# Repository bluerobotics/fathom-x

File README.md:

# Fathom-X and Fathom-E

The Fathom-X and -E Tether Boards are part of Blue Robotics' *Fathom Tether* system. These boards provide interfaces and functionality for the communication methods used with the tether. With the Fathom tether, it is quick and easy to get up and running and interface with your ROV or other application.

The schematic and board layout are designed in EagleCAD.

# Fathom-E (Simple Ethernet) Hardware

## Description

The Fathom-E board provides a simple and economical way to connect the Fathom Tether or a Cat5 cable to an Ethernet jack. It uses all four twisted pairs in the cable and works for tether lengths of up to 100m (per the Ethernet specification).

# Fathom-X Hardware

The Fathom-X board has a few advantages over the Fathom-E interface. It uses a HomePlugAV (IEEE1901) module to send 100 Mbps Ethernet with a single twisted pair. This robust connection works over at least 300m tether lengths. 

Please see the [official documentation](http://docs.bluerobotics.com/fathom-x/) for more information.

## License

The Fathom Ethernet Hardware Design is released under the MIT License.

## Revision History

### Fathom-E 

rev1 - Works but RJ45 misaligned

rev2 - Production version

### Fathom-X

rev1 - Works but poor tether connector used

rev2 - Production version with updated connector

RevB - In progress

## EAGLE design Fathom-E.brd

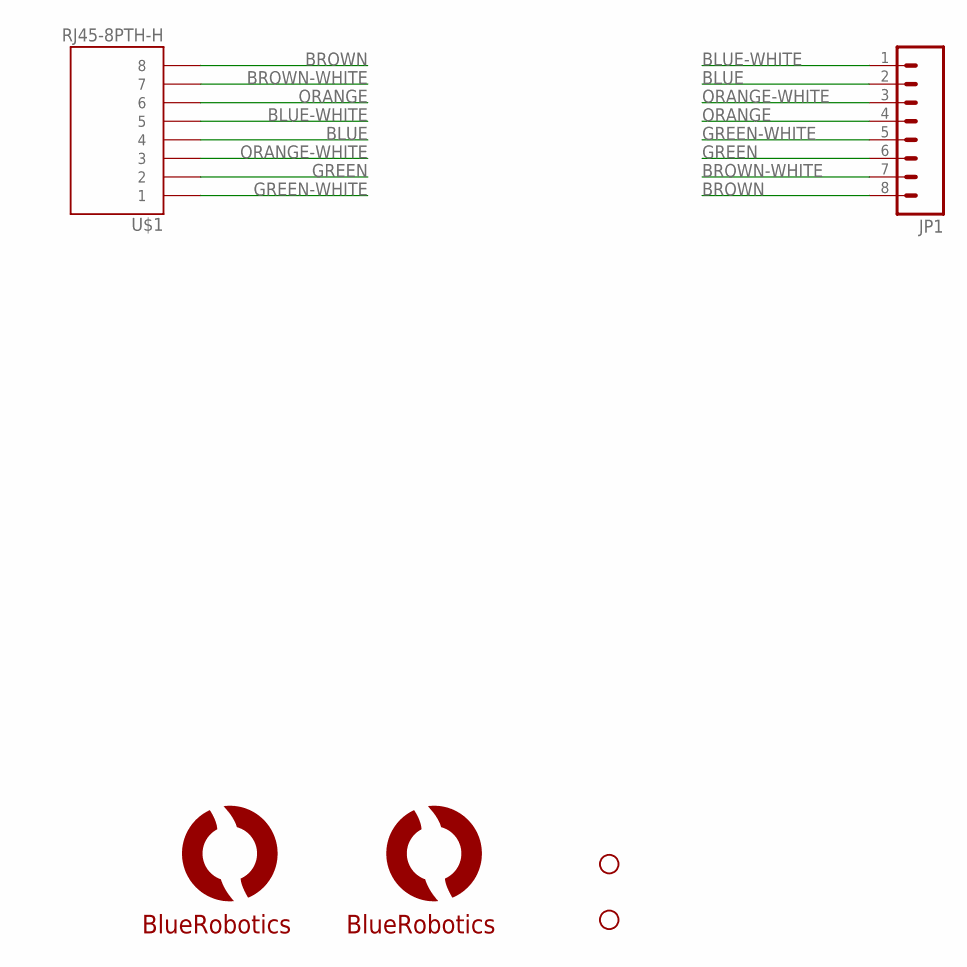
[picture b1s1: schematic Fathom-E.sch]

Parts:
JP1: M083.5MM-8; SCREWTERMINAL-3.5MM-8
STANDOFF2, STANDOFF3: STAND-OFF
U$1: RJ45-8PTH-H; RJ45-8
U$6: LOGOBR-LOGO-MS-COPPER; BR-LOGO-MEDIUM-SMALL-COPPER
U$7: LOGOFULL-M; BR-FULL-LOGO-MEDIUM

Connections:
BLUE: JP1.2, U$1.4
BLUE-WHITE: JP1.1, U$1.5
BROWN: JP1.8, U$1.8
BROWN-WHITE: JP1.7, U$1.7
GREEN: JP1.6, U$1.2
GREEN-WHITE: JP1.5, U$1.1
ORANGE: JP1.4, U$1.6
ORANGE-WHITE: JP1.3, U$1.3

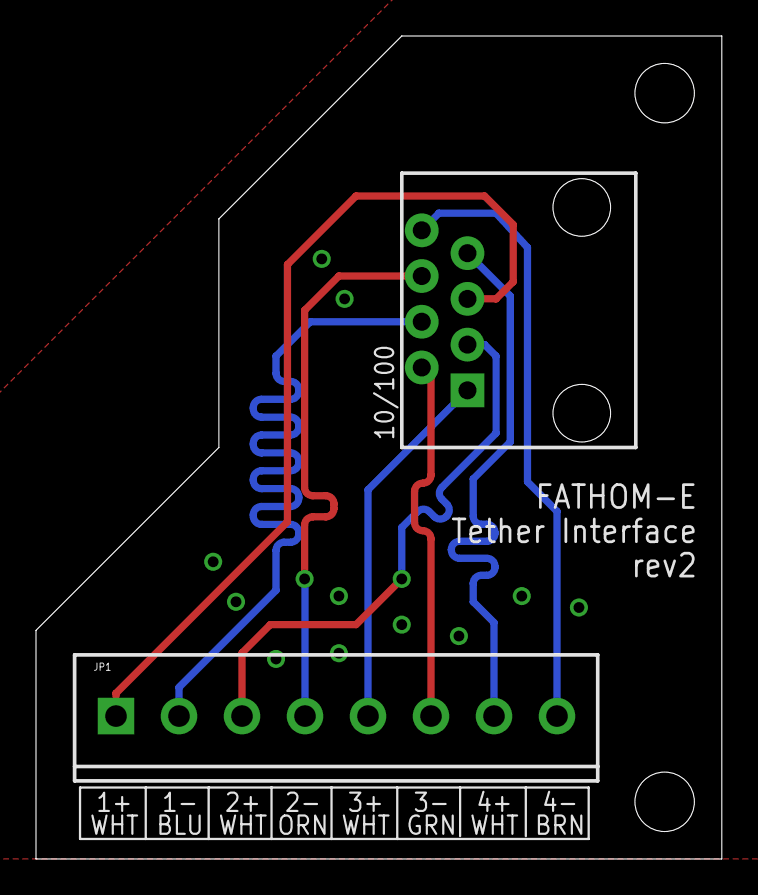
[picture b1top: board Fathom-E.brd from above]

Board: 2 copper layers, 38.1 x 45.7 mm, 6 parts (1 on the bottom side), 8 nets.

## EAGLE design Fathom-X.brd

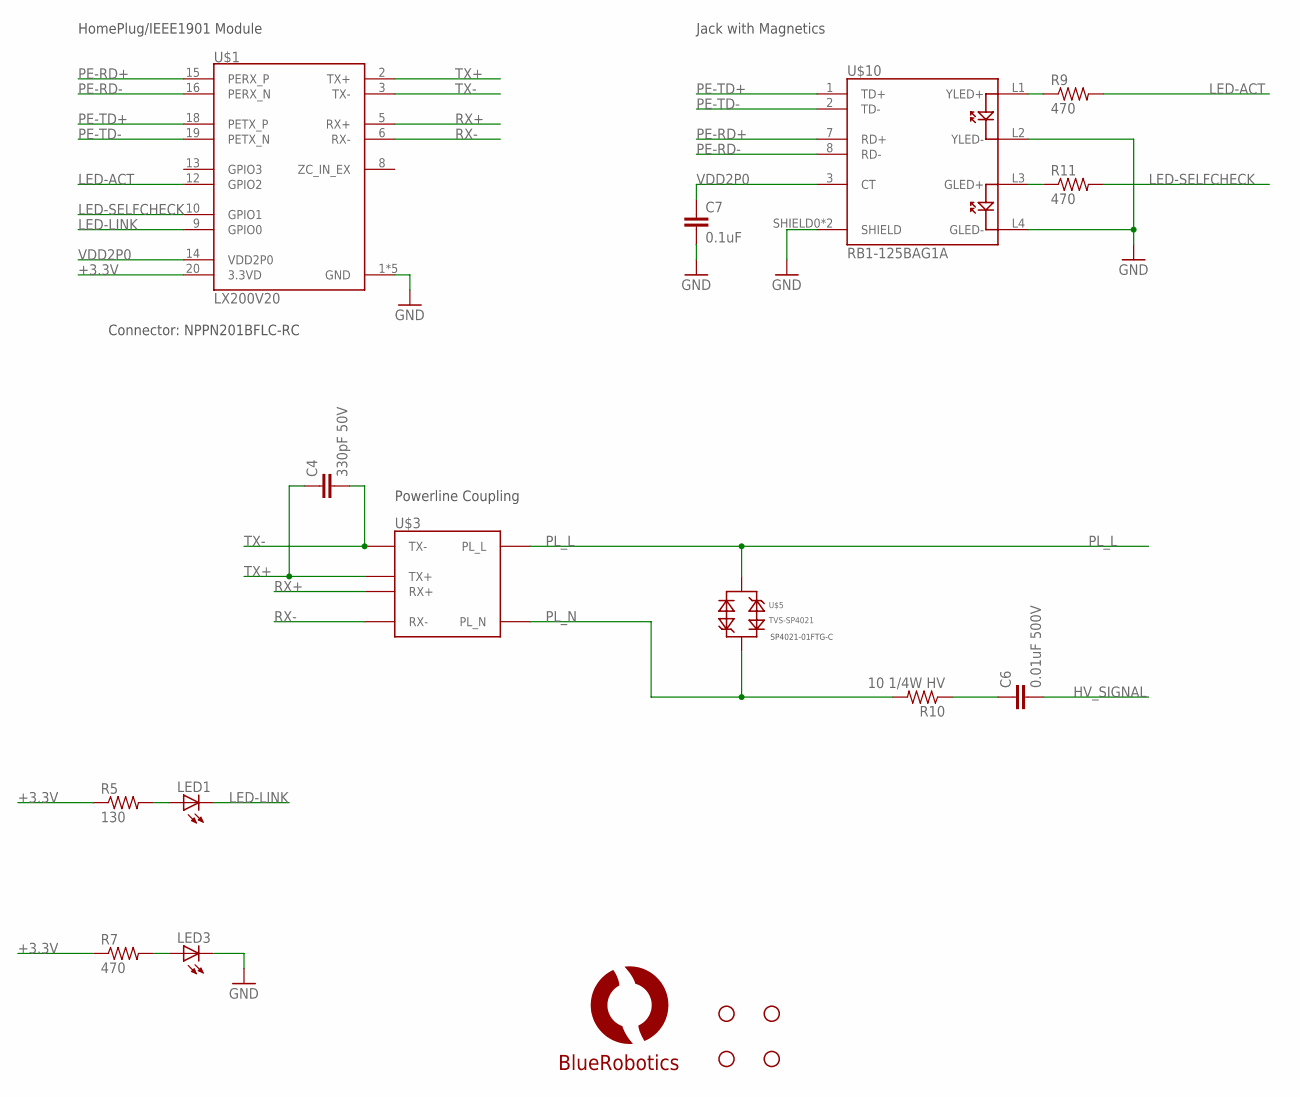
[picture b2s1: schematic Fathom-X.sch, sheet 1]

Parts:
C4: 330pF 50V; C0805
C6: 0.01uF 500V; C1206
C7: 0.1uF; C0603
LED1, LED3: LEDCHIPLED_0603; CHIPLED_0603
R5: 130; R0603
R7, R9, R11: 470; R0603
R10: 10 1/4W HV; R1206
STANDOFF1, STANDOFF2, STANDOFF3, STANDOFF5: STAND-OFF
U$1: LX200V20
U$3: UT11403S
U$5: TVS-SP4021; SOD323-BIDIRECTIONAL
U$6: LOGOBR-LOGO-MS-COPPER; BR-LOGO-MEDIUM-SMALL-COPPER
U$10: RB1-125BAG1A; RJ45-MAG-WIZNET

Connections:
+3.3V: R5.1, R7.1, U$1.20 (3.3VD); also elsewhere on the board
GND: C7.2, LED3.C, U$1.1 (GND), U$1.4 (GND), U$1.7 (GND), U$1.11 (GND), U$1.17 (GND), U$10.L2 (YLED-), U$10.L4 (GLED-), U$10.SHIELD0 (SHIELD), U$10.SHIELD1 (SHIELD); also elsewhere on the board
HV_SIGNAL: C6.2; also elsewhere on the board
LED-ACT: R9.2, U$1.12 (GPIO2)
LED-LINK: LED1.C, U$1.9 (GPIO0)
LED-SELFCHECK: R11.2, U$1.10 (GPIO1)
unnamed: LED1.A, R5.2
unnamed: LED3.A, R7.2
unnamed: C6.1, R10.1
unnamed: R9.1, U$10.L1 (YLED+)
unnamed: R11.1, U$10.L3 (GLED+)
PE-RD+: U$1.15 (PERX_P), U$10.7 (RD+)
PE-RD-: U$1.16 (PERX_N), U$10.8 (RD-)
PE-TD+: U$1.18 (PETX_P), U$10.1 (TD+)
PE-TD-: U$1.19 (PETX_N), U$10.2 (TD-)
PL_L: U$3.PL_L, U$5.2; also elsewhere on the board
PL_N: R10.2, U$3.PL_N, U$5.1
RX+: U$1.5 (RX+), U$3.RX+
RX-: U$1.6 (RX-), U$3.RX-
TX+: C4.1, U$1.2 (TX+), U$3.TX+
TX-: C4.2, U$1.3 (TX-), U$3.TX-
VDD2P0: C7.1, U$1.14 (VDD2P0), U$10.3 (CT)

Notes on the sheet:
SP4021-01FTG-C
Connector: NPPN201BFLC-RC
HomePlug/IEEE1901 Module
Jack with Magnetics
Powerline Coupling

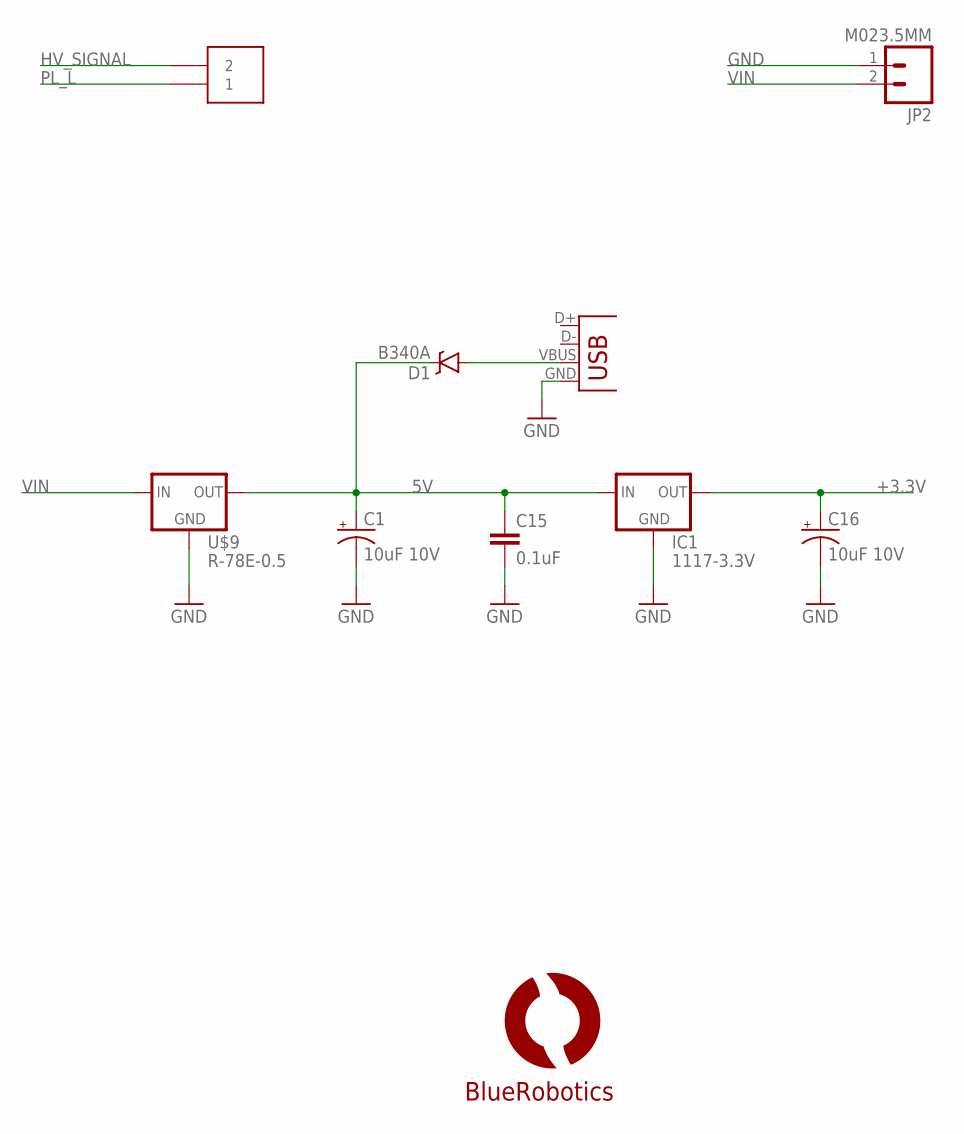
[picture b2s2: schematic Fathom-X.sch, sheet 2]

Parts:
C1, C16: 10uF 10V; EIA3216
C15: 0.1uF; 0603-CAP
D1: B340A; SMA-DIODE
IC1: 1117-3.3V; SOT223
JP2: M023.5MM; SCREWTERMINAL-3.5MM-2
JP3: USBSMD; USB-MINIB
U$7: LOGOFULL-M; BR-FULL-LOGO-MEDIUM
U$8: HEADER-210.16MM; HEADER-10.16MM-2POS
U$9: R-78E-0.5

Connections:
5V: C1.A (+), C15.1, D1.C, IC1.3 (IN), U$9.VOUT (OUT)
+3.3V: C16.A (+), IC1.2 (OUT); also elsewhere on the board
GND: C1.C (-), C15.2, C16.C (-), IC1.1 (GND), JP2.1, JP3.GND, U$9.GND; also elsewhere on the board
HV_SIGNAL: U$8.P$2 (2); also elsewhere on the board
unnamed: D1.A, JP3.VBUS
PL_L: U$8.P$1 (1); also elsewhere on the board
VIN: JP2.2, U$9.VIN (IN)

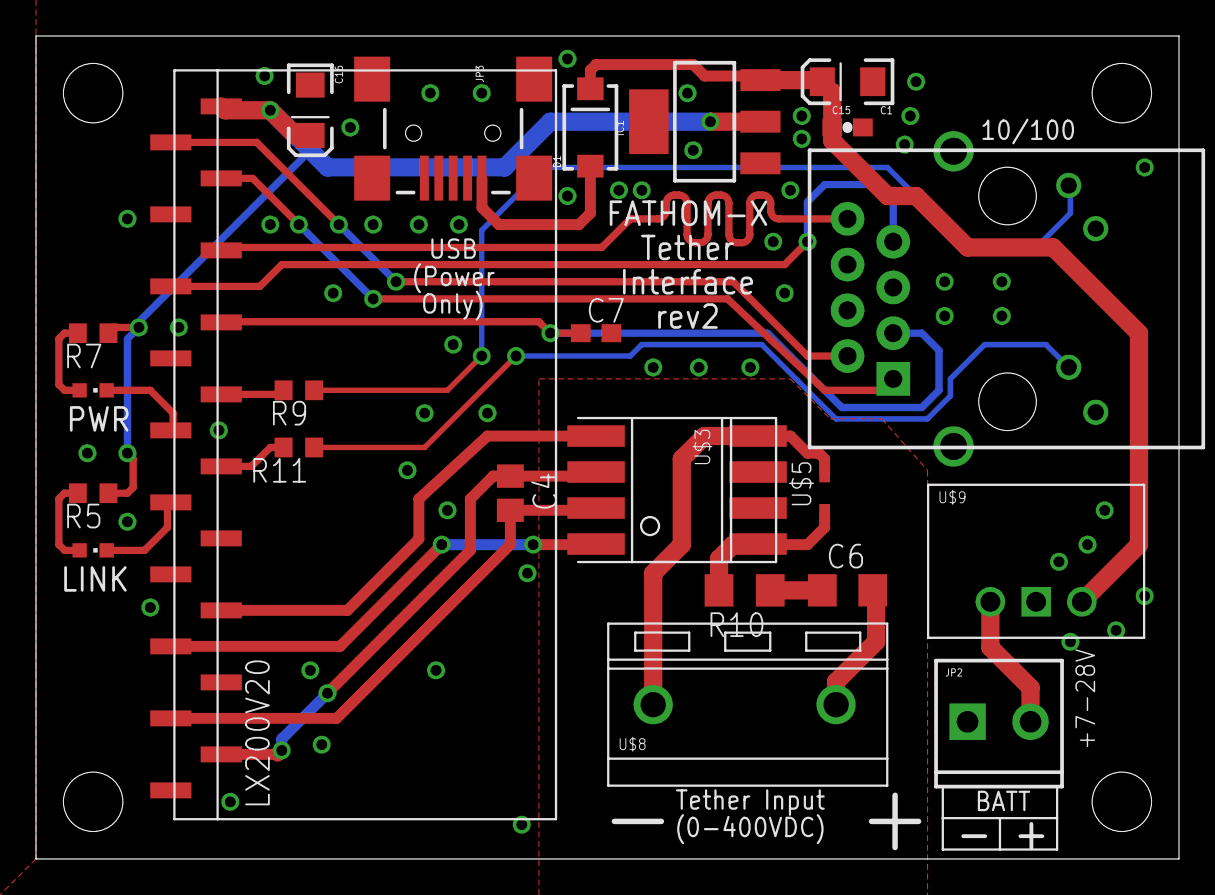
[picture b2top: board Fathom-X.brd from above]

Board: 2 copper layers, 63.5 x 45.7 mm, 29 parts (1 on the bottom side), 25 nets.

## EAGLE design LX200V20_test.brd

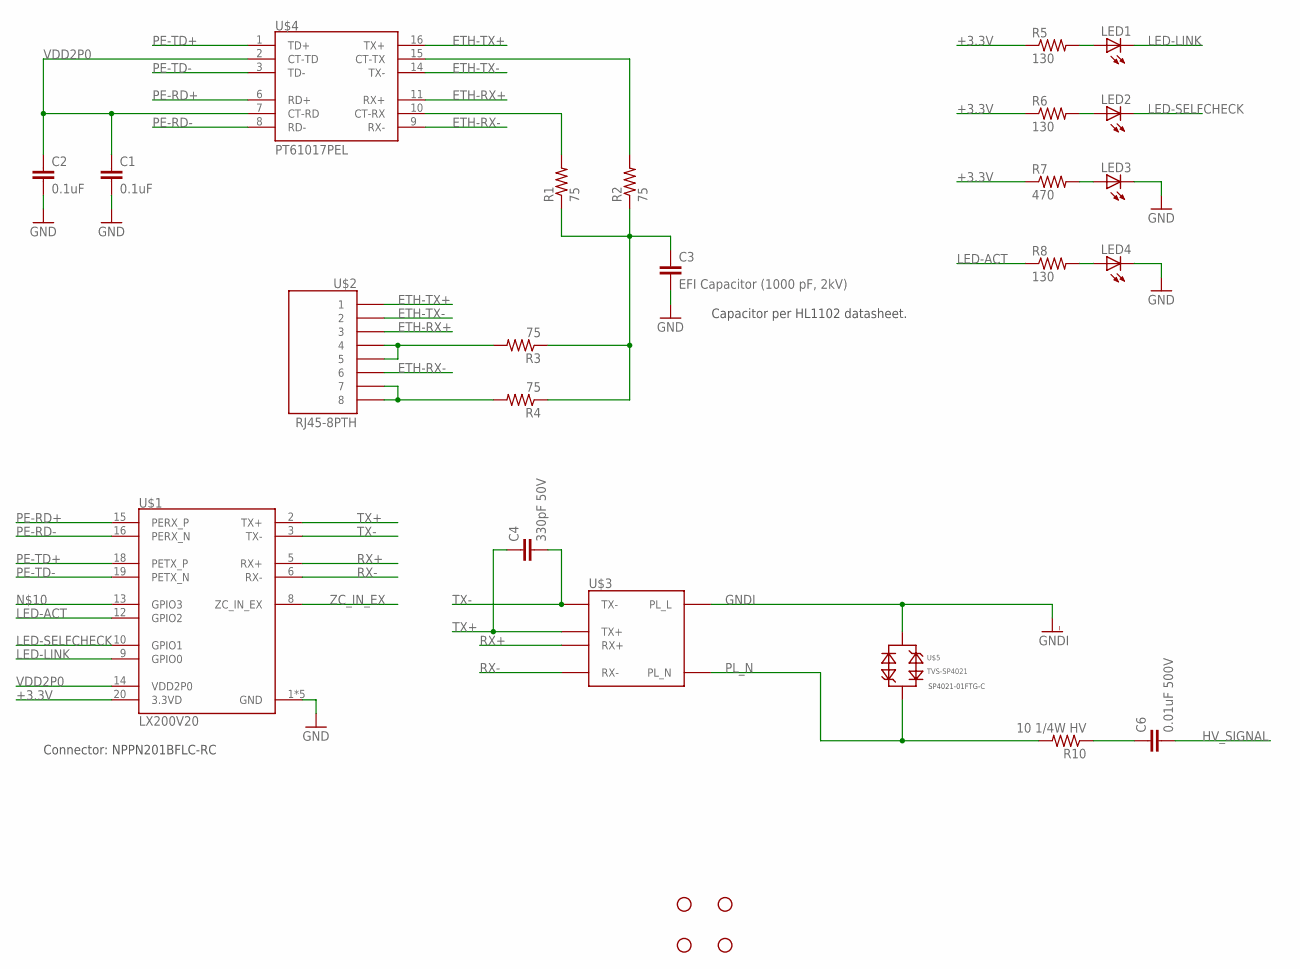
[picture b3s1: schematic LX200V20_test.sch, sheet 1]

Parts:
C1, C2: 0.1uF; C0402
C3: EFI Capacitor (1000 pF, 2kV); C1206
C4: 330pF 50V; C0805
C6: 0.01uF 500V; C1206
LED1, LED2, LED3, LED4: LEDCHIPLED_0603; CHIPLED_0603
R1, R2, R3, R4: 75; R0603
R5, R6, R8: 130; R0603
R7: 470; R0603
R10: 10 1/4W HV; R1206
STANDOFF1, STANDOFF2, STANDOFF3, STANDOFF5: STAND-OFF
U$1: LX200V20
U$2: RJ45-8PTH; RJ45-8-VERT
U$3: UT11403S
U$4: PT61017PEL; PT61017PL
U$5: TVS-SP4021; SOD323-BIDIRECTIONAL

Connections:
+3.3V: R5.1, R6.1, R7.1, U$1.20 (3.3VD)
ETH-RX+: U$2.3, U$4.11 (RX+)
ETH-RX-: U$2.6, U$4.9 (RX-)
ETH-TX+: U$2.1, U$4.16 (TX+)
ETH-TX-: U$2.2, U$4.14 (TX-)
GND: C1.2, C2.2, C3.2, LED3.C, LED4.C, U$1.1 (GND), U$1.4 (GND), U$1.7 (GND), U$1.11 (GND), U$1.17 (GND); also elsewhere on the board
GNDI: U$3.PL_L, U$5.2; also elsewhere on the board
HV_SIGNAL: C6.2; also elsewhere on the board
LED-ACT: R8.1, U$1.12 (GPIO2)
LED-LINK: LED1.C, U$1.9 (GPIO0)
LED-SELFCHECK: LED2.C, U$1.10 (GPIO1)
unnamed: R1.2, U$4.10 (CT-RX)
unnamed: R2.2, U$4.15 (CT-TX)
unnamed: R4.2, U$2.7, U$2.8
unnamed: C3.1, R1.1, R2.1, R3.1, R4.1
unnamed: R3.2, U$2.4, U$2.5
unnamed: LED1.A, R5.2
unnamed: LED2.A, R6.2
unnamed: LED3.A, R7.2
unnamed: LED4.A, R8.2
unnamed: C6.1, R10.1
PE-RD+: U$1.15 (PERX_P), U$4.6 (RD+)
PE-RD-: U$1.16 (PERX_N), U$4.8 (RD-)
PE-TD+: U$1.18 (PETX_P), U$4.1 (TD+)
PE-TD-: U$1.19 (PETX_N), U$4.3 (TD-)
PL_N: R10.2, U$3.PL_N, U$5.1
RX+: U$1.5 (RX+), U$3.RX+
RX-: U$1.6 (RX-), U$3.RX-
TX+: C4.1, U$1.2 (TX+), U$3.TX+
TX-: C4.2, U$1.3 (TX-), U$3.TX-
VDD2P0: C1.1, C2.1, U$1.14 (VDD2P0), U$4.2 (CT-TD), U$4.7 (CT-RD)
ZC_IN_EX: U$1.8 (ZC_IN_EX)

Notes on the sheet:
Capacitor per HL1102 datasheet.
SP4021-01FTG-C
Connector: NPPN201BFLC-RC

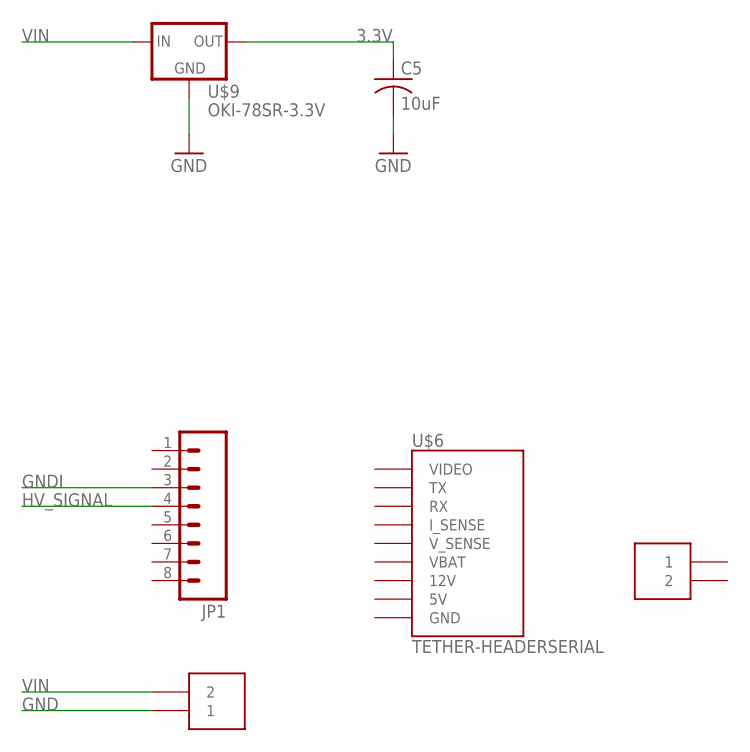
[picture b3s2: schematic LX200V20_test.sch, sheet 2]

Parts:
C5: 10uF; C1206
JP1: M083.5MM-8; SCREWTERMINAL-3.5MM-8
U$6: TETHER-HEADERSERIAL; TETHER-HEADER-2X7
U$7, U$8: HEADER-2POWER; TETHER-POWER-TERMINALS
U$9: OKI-78SR-3.3V; OKI-78SR

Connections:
3.3V: C5.1, U$9.OUTPUT (OUT)
GND: C5.2, U$7.1A (1), U$7.1B (1), U$9.GND; also elsewhere on the board
GNDI: JP1.3; also elsewhere on the board
HV_SIGNAL: JP1.4; also elsewhere on the board
VIN: U$7.2A (2), U$7.2B (2), U$9.INPUT (IN)

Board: 2 copper layers, 33 parts (0 on the bottom side), 33 nets, no tracks yet.

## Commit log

2016-01-27 Base files for Fathom-E.
2016-02-02 First rough layout.
2016-02-03 Updated layout.
2016-02-08 Removed AC components for DC-only support.
2016-02-25 Changing to Ethernet+Power only design.
2016-03-24 Divide to Fathom-E and Fathom-X. Both boards of this revision were ordered.
2016-03-24 Fathom-X: Update signal connector
2016-03-31 Change connector.
2016-04-05 X: Update before order.
2016-05-05 Updated RJ45 position on Fathom-E
2016-06-14 Add Fathom-X schematic.
2016-06-14 Minor Fathom-E change.
2016-06-14 Major update of README.
2016-06-14 Added version notes.
2024-09-19 RevB init
2024-09-19 work
2024-09-19 clean
2024-09-20 did work
2024-09-25 Updated Fathom-X Eagle parts to Kicad

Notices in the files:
parts and their libraries:
SparkFun-Electromechanical: Licensing: Creative Commons ShareAlike 4.0 International - https://creativecommons.org/licenses/by-sa/4.0
